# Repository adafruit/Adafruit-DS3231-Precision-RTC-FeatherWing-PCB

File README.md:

## DS3231 Precision RTC FeatherWing - RTC Add-on PCB
<a href="http://www.adafruit.com/products/3028"><br/>
Click here to purchase one from the Adafruit shop</a>

A Feather board without ambition is a Feather board without FeatherWings! This is the DS3231 Precision RTC FeatherWing: it adds an extremely accurate I2C-integrated Real Time Clock (RTC) with a Temperature Compensated Crystal Oscillator (TCXO)  to any Feather main board. This RTC is the most precise you can get in a small, low power package. Using our Feather Stacking Headers or Feather Female Headers you can connect a FeatherWing on top of your Feather board and let the board take flight!

Most RTCs use an external 32kHz timing crystal that is used to keep time with low current draw. And that's all well and good, but those crystals have slight drift, particularly when the temperature changes (the temperature changes the oscillation frequency very very very slightly but it does add up!) This RTC is in a beefy package because the crystal is inside the chip! And right next to the integrated crystal is a temperature sensor. That sensor compensates for the frequency changes by adding or removing clock ticks so that the timekeeping stays on schedule.

PCB files for the DS3231 Precision RTC FeatherWing. The format is EagleCAD schematic and board layout
- https://www.adafruit.com/products/3028

### License

Adafruit invests time and resources providing this open source design, please support Adafruit and open-source hardware by purchasing products from [Adafruit](https://www.adafruit.com)!

All text above must be included in any redistribution

Designed by Limor Fried/Ladyada for Adafruit Industries.
Creative Commons Attribution/Share-Alike, all text above must be included in any redistribution. 
See license.txt for additional information.

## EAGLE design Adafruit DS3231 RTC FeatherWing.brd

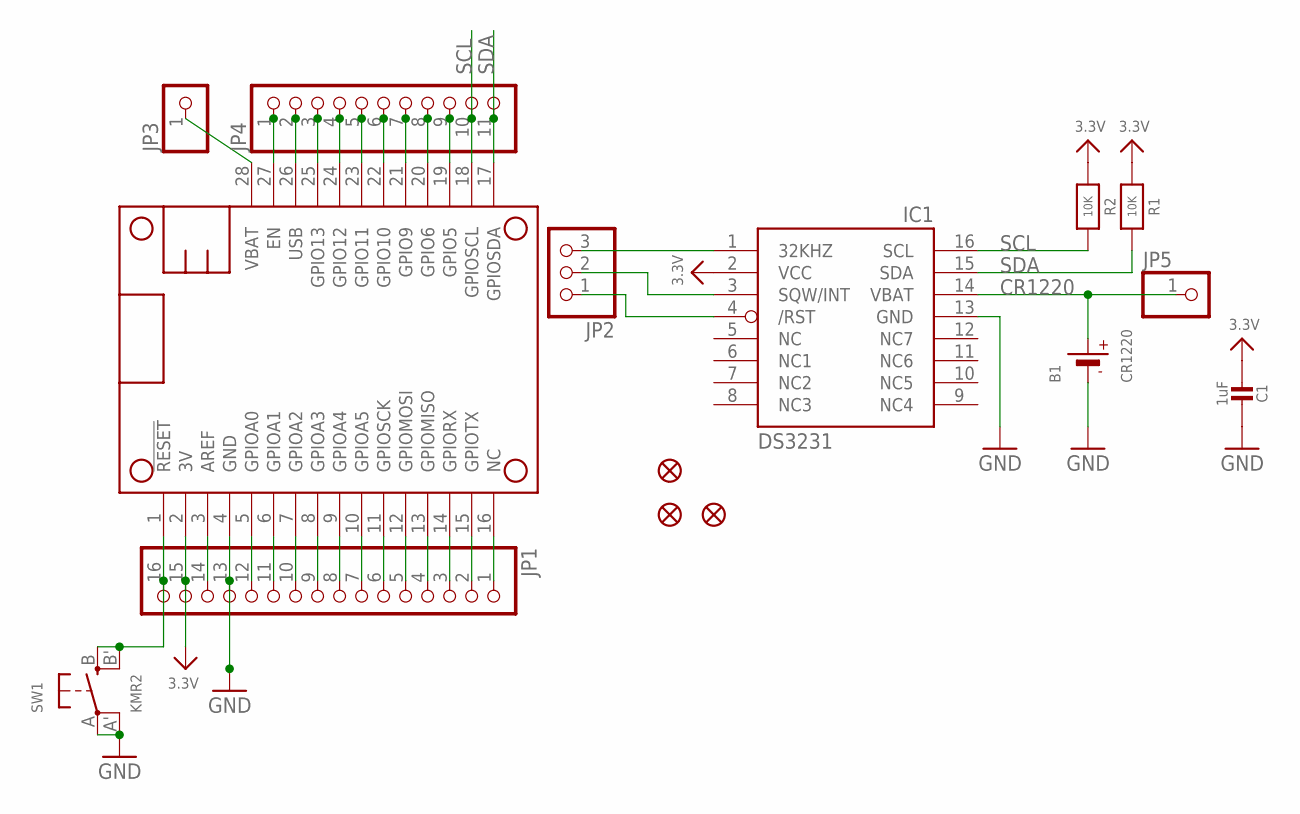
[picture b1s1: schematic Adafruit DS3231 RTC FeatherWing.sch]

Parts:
B1: CR1220; CR1220-2
C1: 1uF; 0805-NO
FID1, FID2, FID3: FIDUCIAL""; FIDUCIAL_1MM
IC1: DS3231/SO; SO16W
JP1: HEADER-1X16ROUND; 1X16_ROUND
JP2: HEADER-1X3ROUND; 1X03_ROUND
JP3, JP5: HEADER-1X1ROUND; 1X01_ROUND
JP4: HEADER-1X11; 1X11_ROUND
MS1: MICROSHIELD_NODIM; MICROSHIELD_DIM
R1, R2: 10K; 0805-NO
SW1: KMR2; BTN_KMR2_4.6X2.8

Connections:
3.3V: C1.2, IC1.2 (VCC), JP1.15, MS1.2 (3V), R1.1, R2.1
32KHZ: IC1.1 (32KHZ), JP2.3
!RTC_RST: IC1.4 (/RST), JP2.1
CR1220: B1.+, IC1.14 (VBAT), JP5.1
GND: B1.-, C1.1, IC1.13 (GND), JP1.13, MS1.4 (GND), SW1.A, SW1.A' (P1)
unnamed: JP1.1, MS1.16 (NC)
unnamed: JP1.2, MS1.15 (GPIOTX)
unnamed: JP1.3, MS1.14 (GPIORX)
unnamed: JP1.4, MS1.13 (GPIOMISO)
unnamed: JP1.5, MS1.12 (GPIOMOSI)
unnamed: JP1.6, MS1.11 (GPIOSCK)
unnamed: JP1.7, MS1.10 (GPIOA5)
unnamed: JP1.8, MS1.9 (GPIOA4)
unnamed: JP1.9, MS1.8 (GPIOA3)
unnamed: JP1.10, MS1.7 (GPIOA2)
unnamed: JP1.11, MS1.6 (GPIOA1)
unnamed: JP1.12, MS1.5 (GPIOA0)
unnamed: JP4.1, MS1.27 (EN)
unnamed: JP4.3, MS1.25 (GPIO13)
unnamed: JP4.4, MS1.24 (GPIO12)
unnamed: JP4.5, MS1.23 (GPIO11)
unnamed: JP4.6, MS1.22 (GPIO10)
unnamed: JP4.7, MS1.21 (GPIO9)
unnamed: JP4.8, MS1.20 (GPIO6)
unnamed: JP4.9, MS1.19 (GPIO5)
unnamed: JP1.14, MS1.3 (AREF)
unnamed: JP1.16, MS1.1 (!RESET), SW1.B (S), SW1.B' (S1)
SCL: IC1.16 (SCL), JP4.10, MS1.18 (GPIOSCL), R2.2
SDA: IC1.15 (SDA), JP4.11, MS1.17 (GPIOSDA), R1.2
SQW: IC1.3 (SQW/INT), JP2.2
USB: JP4.2, MS1.26 (USB)
VBAT: JP3.1, MS1.28 (VBAT)

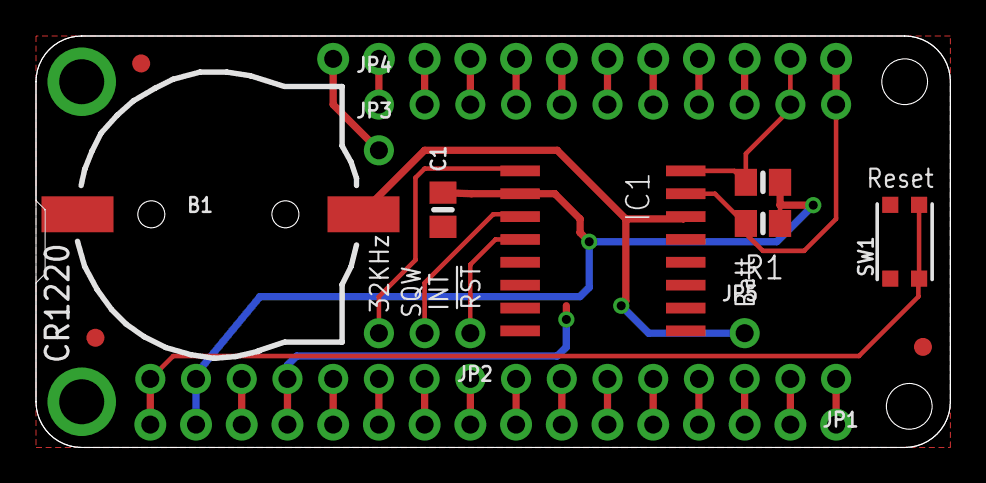
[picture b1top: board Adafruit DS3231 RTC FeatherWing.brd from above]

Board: 2 copper layers, 50.8 x 22.9 mm, 16 parts (1 on the bottom side), 32 nets.

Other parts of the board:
U$6: FEATHERLOGO

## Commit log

2016-06-19 initty

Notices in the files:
parts and their libraries:
microbuilder: This work is placed in the public domain, and may be freely used for commercial and non-commercial work with the following conditions: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
